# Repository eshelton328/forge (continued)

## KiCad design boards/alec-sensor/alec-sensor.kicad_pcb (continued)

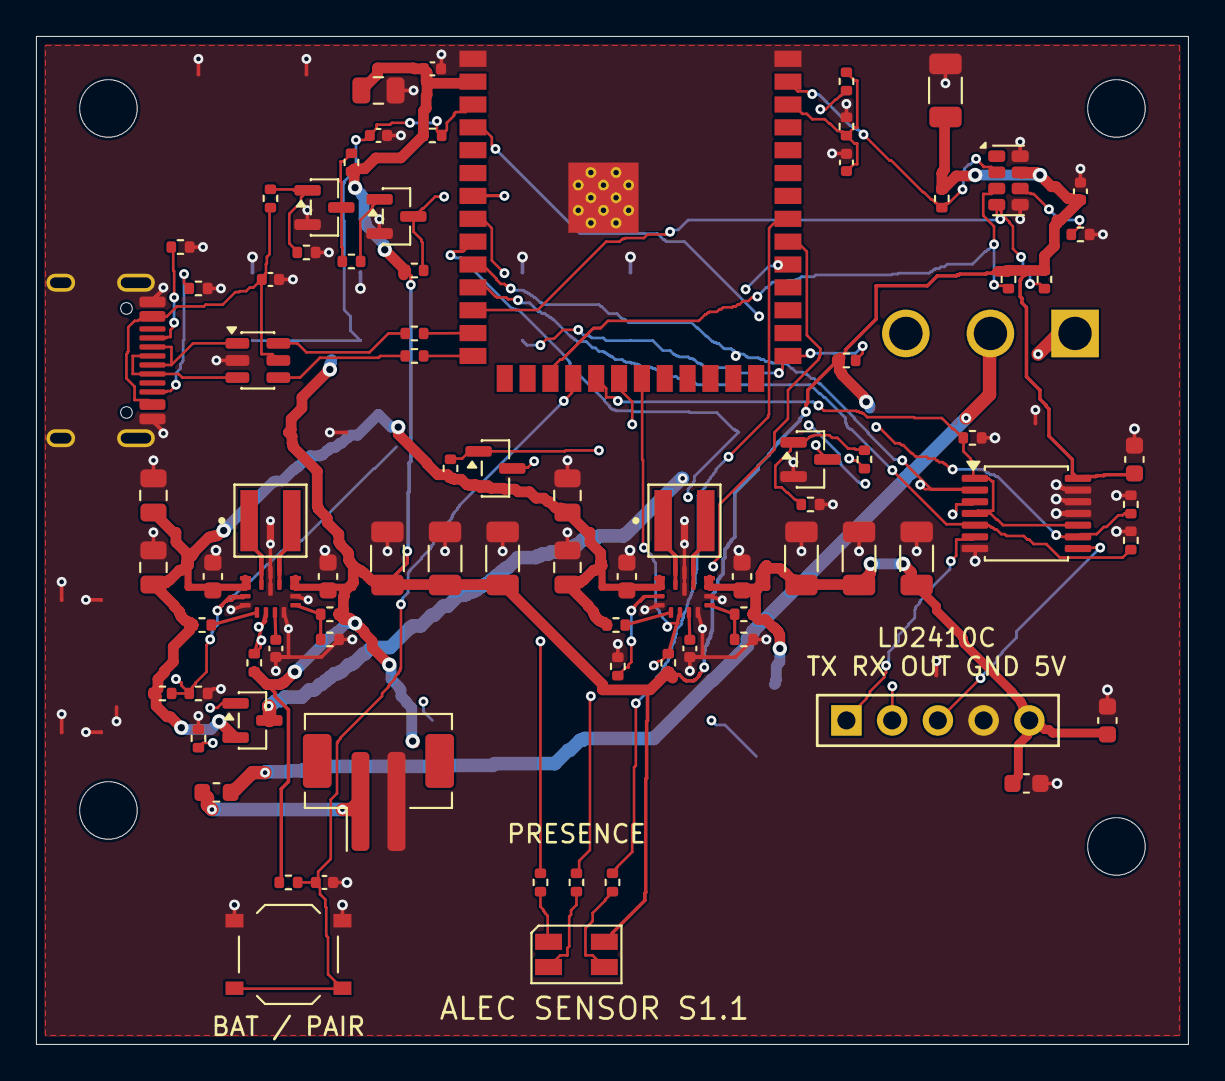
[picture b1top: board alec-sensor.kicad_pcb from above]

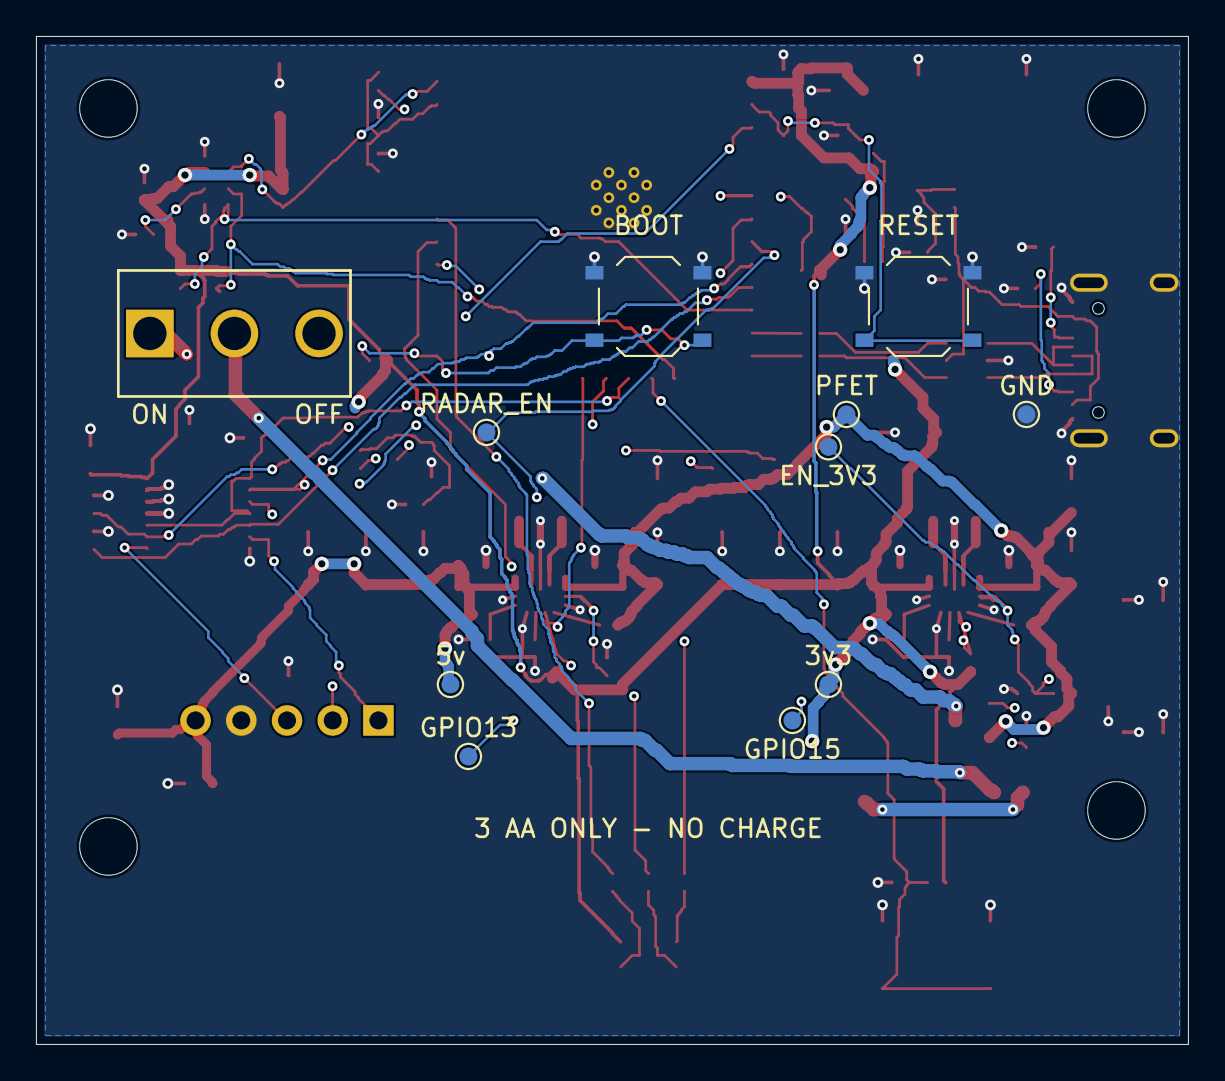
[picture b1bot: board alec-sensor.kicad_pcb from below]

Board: 4 copper layers, 64.0 x 56.0 mm, 100 parts (11 on the bottom side), 60 nets.

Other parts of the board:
H1, H2, H3, H4: M3; MountingHole_3.2mm_M3
TP1: GND; TestPoint_Pad_D1.0mm
TP2: PFET; TestPoint_Pad_D1.0mm
TP3: 3v3; TestPoint_Pad_D1.0mm
TP4: 5v; TestPoint_Pad_D1.0mm
TP5: GPIO15; TestPoint_Pad_D1.0mm
TP6: GPIO13; TestPoint_Pad_D1.0mm
TP7: EN_3V3; TestPoint_Pad_D1.0mm
TP8: RADAR_EN; TestPoint_Pad_D1.0mm

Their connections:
/3v3: TP3.1; also elsewhere on the board
/5v: TP4.1; also elsewhere on the board
/EN_3V3: TP7.1; also elsewhere on the board
/GPIO13: TP6.1; also elsewhere on the board
/GPIO15: TP5.1; also elsewhere on the board
/PFET: TP2.1; also elsewhere on the board
/RADAR_EN: TP8.1; also elsewhere on the board
GND: TP1.1; also elsewhere on the board

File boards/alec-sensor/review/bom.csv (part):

Reference,Value,MPN,Footprint,Voltage,Datasheet,Assembly,Manufacturer,LCSC#
C1,10µF,GRM21BR61E106KA73L,Capacitor_SMD:C_0805_2012Metric,25V,https://www.lcsc.com/datasheet/lcsc_datasheet_2304140030_Mur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,Selected prototype part; package/assembly release checks remain,Murata Electronics,C84416
C10,10µF,GRM21BR61E106KA73L,Capacitor_SMD:C_0805_2012Metric,25V,https://www.lcsc.com/datasheet/lcsc_datasheet_2304140030_Mur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,Selected prototype part; package/assembly release checks remain,Murata Electronics,C84416
C11,10µF,GRT188R61A106KE13D,Capacitor_SMD:C_0603_1608Metric,10V,https://search.murata.co.jp/Ceramy/image/img/A01X/G101/ENG/G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,Selected prototype part; package/assembly release checks remain,Murata Electronics,C782172
C12,0.1µF,GRM155R71C104KA88D,Capacitor_SMD:C_0402_1005Metric,16V,https://www.lcsc.com/datasheet/lcsc_datasheet_1811081616_Mur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,Selected prototype part; package/assembly release checks remain,Murata Electronics,C71629
C13,10µF,GRT188R61A106KE13D,Capacitor_SMD:C_0603_1608Metric,10V,https://search.murata.co.jp/Ceramy/image/img/A01X/G101/ENG/G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,Selected prototype part; package/assembly release checks remain,Murata Electronics,C782172
C14,22µF,GRM31CR61C226KE15L,Capacitor_SMD:C_1206_3216Metric,16V,https://www.lcsc.com/datasheet/lcsc_datasheet_2304140030_Mur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,Selected prototype part; package/assembly release checks remain,Murata Electronics,C77088
C15,22µF,GRM31CR61C226KE15L,Capacitor_SMD:C_1206_3216Metric,16V,https://www.lcsc.com/datasheet/lcsc_datasheet_2304140030_Mur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,Selected prototype part; package/assembly release checks remain,Murata Electronics,C77088
C16,22µF,GRM31CR61C226KE15L,Capacitor_SMD:C_1206_3216Metric,16V,https://www.lcsc.com/datasheet/lcsc_datasheet_2304140030_Mur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,Selected prototype part; package/assembly release checks remain,Murata Electronics,C77088
C17,22µF,GRM21BR61A226ME44L,Capacitor_SMD:C_0805_2012Metric,10V,https://www.lcsc.com/datasheet/lcsc_datasheet_2410010301_Mur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,Selected prototype part; package/assembly release checks remain,Murata Electronics,C441864
C18,0.1µF,GRM155R71C104KA88D,Capacitor_SMD:C_0402_1005Metric,16V,https://www.lcsc.com/datasheet/lcsc_datasheet_1811081616_Mur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,Selected prototype part; package/assembly release checks remain,Murata Electronics,C71629
C19,1µF,GRM155R61A105KE15D,Capacitor_SMD:C_0402_1005Metric,10V,https://www.lcsc.com/datasheet/lcsc_datasheet_1810201320_Mur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,Selected prototype part; package/assembly release checks remain,Murata Electronics,C76999
C2,10µF,GRM21BR61E106KA73L,Capacitor_SMD:C_0805_2012Metric,25V,https://www.lcsc.com/datasheet/lcsc_datasheet_2304140030_Mur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,Selected prototype part; package/assembly release checks remain,Murata Electronics,C84416
C20,0.1µF,GRM155R71C104KA88D,Capacitor_SMD:C_0402_1005Metric,16V,https://www.lcsc.com/datasheet/lcsc_datasheet_1811081616_Mur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,Selected prototype part; package/assembly release checks remain,Murata Electronics,C71629
C21,100µF,CL31A107MQHNNNE,Capacitor_SMD:C_1206_3216Metric,6.3V,https://www.lcsc.com/datasheet/lcsc_datasheet_2304140030_Sam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,Selected prototype part; package/assembly release checks remain,Samsung Electro-Mechanics,C15008
C25,0.1µF,GRM155R71C104KA88D,Capacitor_SMD:C_0402_1005Metric,16V,https://www.lcsc.com/datasheet/lcsc_datasheet_1811081616_Mur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,Selected prototype part; package/assembly release checks remain,Murata Electronics,C71629
C29,0.1µF,GRM155R71C104KA88D,Capacitor_SMD:C_0402_1005Metric,16V,https://www.lcsc.com/datasheet/lcsc_datasheet_1811081616_Mur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,Selected prototype part; package/assembly release checks remain,Murata Electronics,C71629
C3,10µF,GRT188R61A106KE13D,Capacitor_SMD:C_0603_1608Metric,10V,https://search.murata.co.jp/Ceramy/image/img/A01X/G101/ENG/G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,Selected prototype part; package/assembly release checks remain,Murata Electronics,C782172
C34,0.1uF,GRM155R71C104KA88D,Capacitor_SMD:C_0402_1005Metric,16V,https://www.lcsc.com/datasheet/lcsc_datasheet_1811081616_Mur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,Selected prototype part; package/assembly release checks remain,Murata Electronics,C71629
C35,10uF,GRT188R61A106KE13D,Capacitor_SMD:C_0603_1608Metric,10V,https://search.murata.co.jp/Ceramy/image/img/A01X/G101/ENG/G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,Selected prototype part; package/assembly release checks remain,Murata Electronics,C782172
C36,0.1uF,GRM188R71C104KA01D,Capacitor_SMD:C_0603_1608Metric,16V,https://wmsc.lcsc.com/wmsc/upload/file/pdf/v2/lcsc/181031111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,Selected prototype part; package/assembly release checks remain,Murata Electronics,C45000
C37,0.1uF,GRM188R71C104KA01D,Capacitor_SMD:C_0603_1608Metric,16V,https://wmsc.lcsc.com/wmsc/upload/file/pdf/v2/lcsc/181031111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,Selected prototype part; package/assembly release checks remain,Murata Electronics,C45000
C4,0.1µF,GRM155R71C104KA88D,Capacitor_SMD:C_0402_1005Metric,16V,https://www.lcsc.com/datasheet/lcsc_datasheet_1811081616_Mur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,Selected prototype part; package/assembly release checks remain,Murata Electronics,C71629
C5,10µF,GRT188R61A106KE13D,Capacitor_SMD:C_0603_1608Metric,10V,https://search.murata.co.jp/Ceramy/image/img/A01X/G101/ENG/G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,Selected prototype part; package/assembly release checks remain,Murata Electronics,C782172
C6,22µF,GRM31CR61C226KE15L,Capacitor_SMD:C_1206_3216Metric,16V,https://www.lcsc.com/datasheet/lcsc_datasheet_2304140030_Mur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,Selected prototype part; package/assembly release checks remain,Murata Electronics,C77088
C7,22µF,GRM31CR61C226KE15L,Capacitor_SMD:C_1206_3216Metric,16V,https://www.lcsc.com/datasheet/lcsc_datasheet_2304140030_Mur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,Selected prototype part; package/assembly release checks remain,Murata Electronics,C77088
C8,22µF,GRM31CR61C226KE15L,Capacitor_SMD:C_1206_3216Metric,16V,https://www.lcsc.com/datasheet/lcsc_datasheet_2304140030_Mur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,Selected prototype part; package/assembly release checks remain,Murata Electronics,C77088
C9,10µF,GRM21BR61E106KA73L,Capacitor_SMD:C_0805_2012Metric,25V,https://www.lcsc.com/datasheet/lcsc_datasheet_2304140030_Mur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,Selected prototype part; package/assembly release checks remain,Murata Electronics,C84416
D2,150141M173100,150141M173100,LED_SMD:LED_RGB_Wuerth-PLCC4_3.2x2.8mm_150141M173100,,https://www.we-online.com/components/products/datasheet/1501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,Selected prototype part; package/assembly release checks remain,Wurth Elektronik,C5342281
F1,1.5A FAST,046701.5NRHF,Fuse:Fuse_0603_1608Metric,,https://www.lcsc.com/datasheet/lcsc_datasheet_2304140030_Lit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,Selected prototype part; package/assembly release checks remain,Littelfuse,C187608
J1,Conn_01x02_Pin,B2B-PH-SM4-TB(LF)(SN),Connector_JST:JST_PH_B2B-PH-SM4-TB_1x02-1MP_P2.00mm_Vertical,,https://www.lcsc.com/datasheet/lcsc_datasheet_2304140030_JST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,Selected prototype part; package/assembly release checks remain,JST,C160352
J2,USB_C_Receptacle_USB2.0_16P,TYPE-C-31-M-12,Board:USB_C_HRO_Overhang,,https://www.lcsc.com/datasheet/lcsc_datasheet_2205251630_Kor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,Selected prototype part; package/assembly release checks remain,Korean Hroparts Elec,C165948
J3,LD2410C — INTERNAL,SSW-105-01-F-S,Sensor:Samtec_SSW-105-01-F-S,,https://www.samtec.com/products/ssw-105-01-f-s,Selected prototype part; package/assembly release checks remain,Samtec,C5930350
L1,1.5µH,XFL4020-152MEC,TPS63070:IND_XFL4020-152MEC,,https://www.coilcraft.com/getmedia/50632d43-da1b-4cdb-8ab4-3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,Selected prototype part; package/assembly release checks remain,Coilcraft,C3033018
L2,1.5µH,XFL4020-152MEC,TPS63070:IND_XFL4020-152MEC,,https://www.coilcraft.com/getmedia/50632d43-da1b-4cdb-8ab4-3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,Selected prototype part; package/assembly release checks remain,Coilcraft,C3033018
Q1,AO3401A,AO3401A,Package_TO_SOT_SMD:SOT-23,,https://www.lcsc.com/datasheet/lcsc_datasheet_2412061733_Alp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,Selected prototype part; package/assembly release checks remain,Alpha & Omega Semicon,C15127
Q4,MMBT3904,MMBT3904LT1G,Package_TO_SOT_SMD:SOT-23,,https://www.onsemi.com/pdf/datasheet/mmbt3904lt1-d.pdf,Selected prototype part; package/assembly release checks remain,onsemi,C81464
Q5,MMBT3904,MMBT3904LT1G,Package_TO_SOT_SMD:SOT-23,,https://www.onsemi.com/pdf/datasheet/mmbt3904lt1-d.pdf,Selected prototype part; package/assembly release checks remain,onsemi,C81464
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
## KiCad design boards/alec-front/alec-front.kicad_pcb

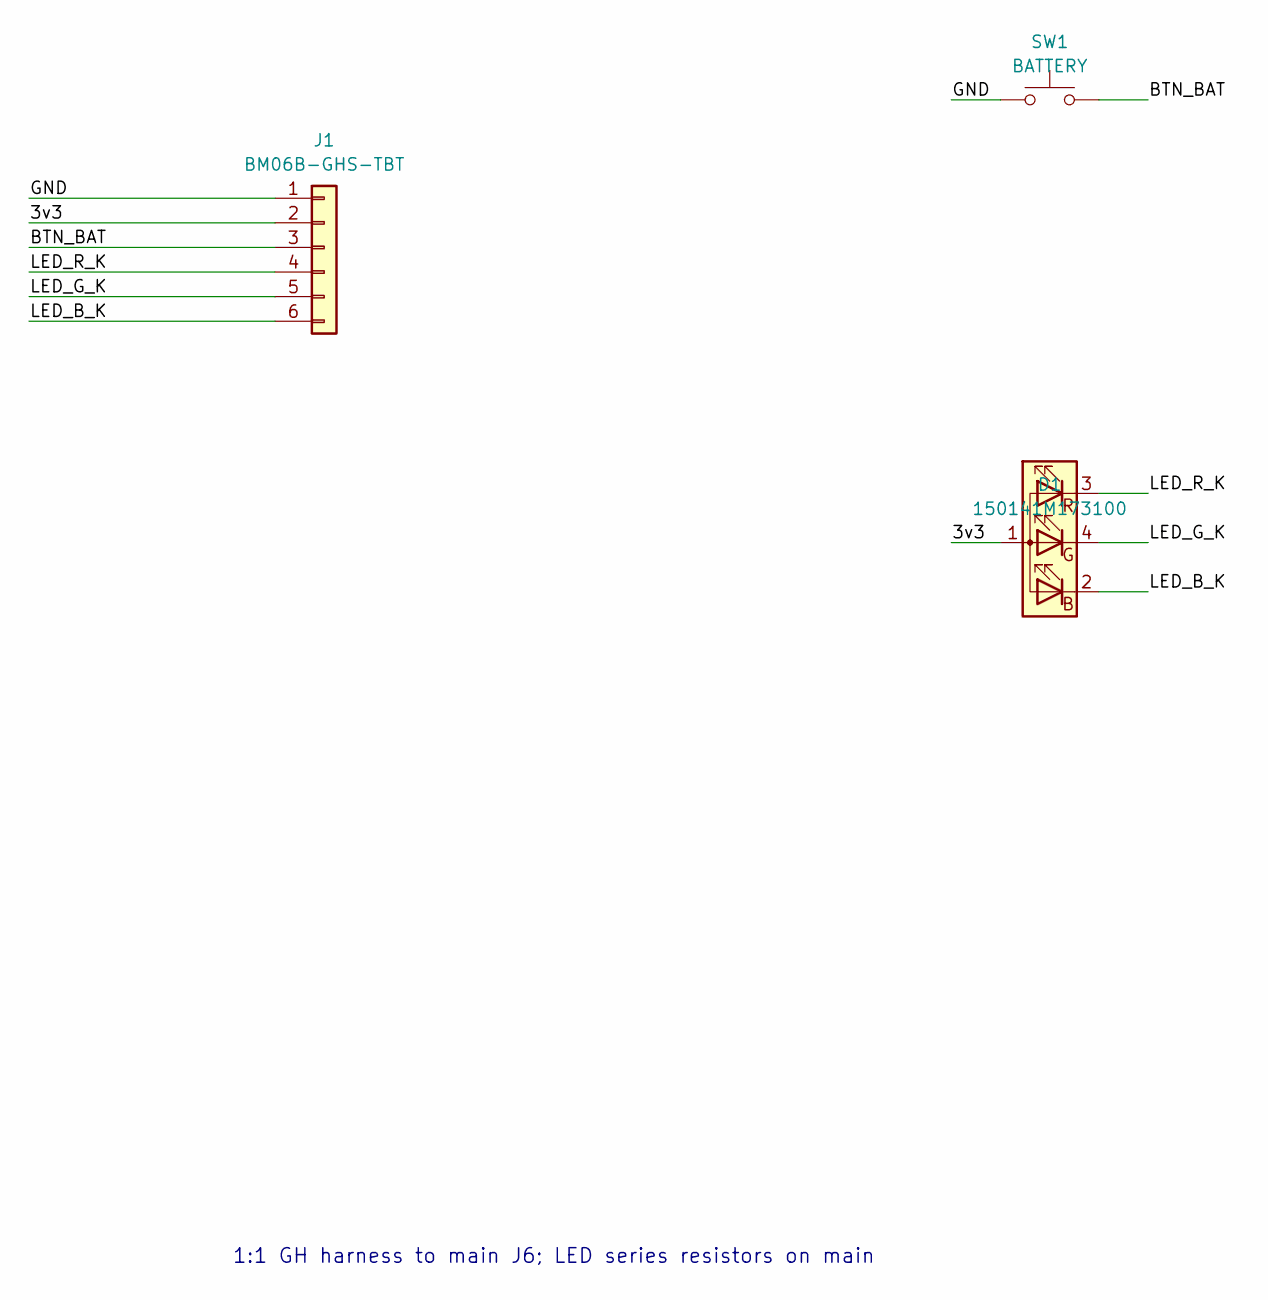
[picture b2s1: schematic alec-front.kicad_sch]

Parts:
D1: 150141M173100; LED_RGB_Wuerth-PLCC4_3.2x2.8mm_150141M173100; MPN 150141M173100; LCSC# C5342281
J1: BM06B-GHS-TBT; JST_GH_BM06B-GHS-TBT_1x06-1MP_P1.25mm_Vertical; MPN BM06B-GHS-TBT(LF)(SN); LCSC# C189892
SW1: BATTERY; SW_SPST_B3U-1000P; MPN B3U-1000P; LCSC# C231329

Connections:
/3v3: D1.1 (A), J1.2
/BTN_BAT: J1.3, SW1.2
/GND: J1.1, SW1.1
/LED_B_K: D1.2 (BK), J1.6
/LED_G_K: D1.4 (GK), J1.5
/LED_R_K: D1.3 (RK), J1.4

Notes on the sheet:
1:1 GH harness to main J6; LED series resistors on main

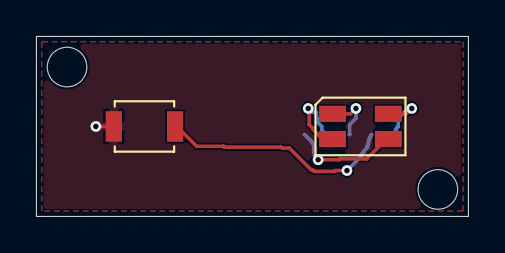
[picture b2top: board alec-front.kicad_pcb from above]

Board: 2 copper layers, 24.0 x 10.0 mm, 5 parts (1 on the bottom side), 6 nets.

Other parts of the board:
H1, H2: MountingHole_2.2mm_M2

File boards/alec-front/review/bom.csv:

Reference,Value,MPN,Footprint,Voltage,Datasheet,Assembly,Manufacturer,LCSC#
D1,150141M173100,150141M173100,LED_SMD:LED_RGB_Wuerth-PLCC4_3.2x2.8mm_150141M173100,,https://www.we-online.com/components/products/datasheet/1501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,Selected prototype part; package/assembly release checks remain,Wurth Elektronik,C5342281
J1,BM06B-GHS-TBT,BM06B-GHS-TBT(LF)(SN),Connector_JST:JST_GH_BM06B-GHS-TBT_1x06-1MP_P1.25mm_Vertical,,https://www.jst-mfg.com/product/pdf/eng/eGH.pdf,Selected prototype part; package/assembly release checks remain,JST,C189892
SW1,BATTERY,B3U-1000P,Button_Switch_SMD:SW_SPST_B3U-1000P,,https://omronfs.omron.com/en_US/ecb/products/pdf/en-b3u.pdf,Selected prototype part; package/assembly release checks remain,Omron Electronics,C231329

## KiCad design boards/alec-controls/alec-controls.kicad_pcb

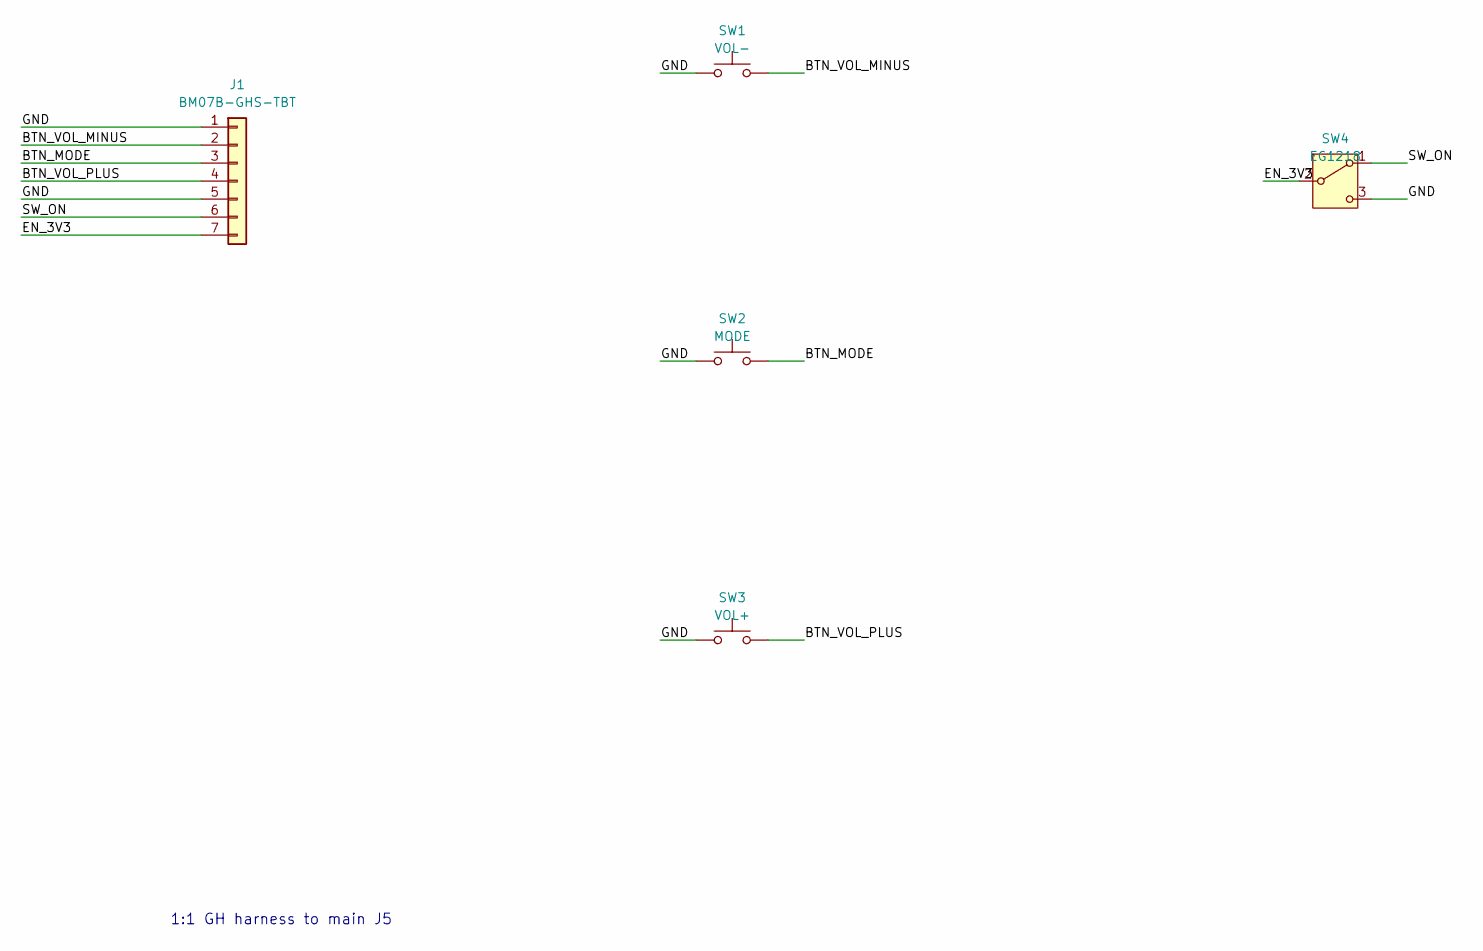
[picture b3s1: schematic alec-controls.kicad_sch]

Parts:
J1: BM07B-GHS-TBT; JST_GH_BM07B-GHS-TBT_1x07-1MP_P1.25mm_Vertical; MPN BM07B-GHS-TBT(LF)(SN); LCSC# C5305068
SW1: VOL-; SW_TH_Tactile_Omron_B3F-106x; MPN B3F-1060; LCSC# C726010
SW2: MODE; SW_TH_Tactile_Omron_B3F-106x; MPN B3F-1060; LCSC# C726010
SW3: VOL+; SW_TH_Tactile_Omron_B3F-106x; MPN B3F-1060; LCSC# C726010
SW4: EG1218; MPN EG1218; LCSC# C273394

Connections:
/BTN_MODE: J1.3, SW2.2
/BTN_VOL_MINUS: J1.2, SW1.2
/BTN_VOL_PLUS: J1.4, SW3.2
/EN_3V3: J1.7, SW4.2 (B)
/GND: J1.1, J1.5, SW1.1, SW2.1, SW3.1, SW4.3 (C)
/SW_ON: J1.6, SW4.1 (A)

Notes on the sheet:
1:1 GH harness to main J5

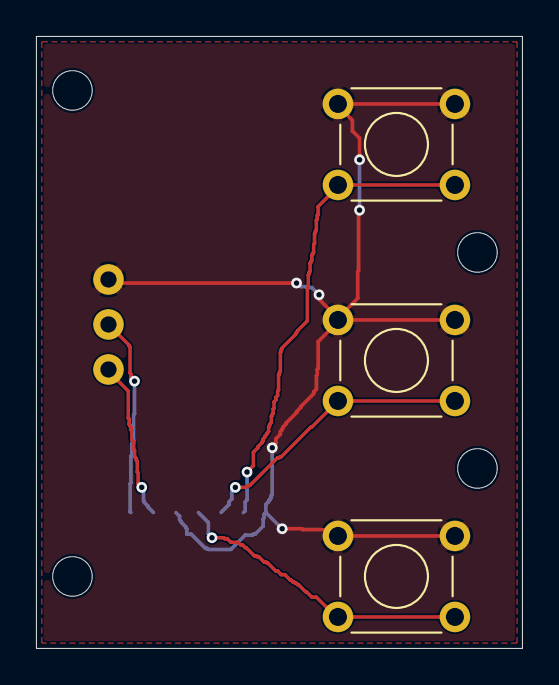
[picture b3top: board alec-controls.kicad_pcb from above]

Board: 2 copper layers, 27.0 x 34.0 mm, 9 parts (1 on the bottom side), 6 nets.

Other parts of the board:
H1, H2, H3, H4: MountingHole_2.2mm_M2

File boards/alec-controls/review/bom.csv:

Reference,Value,MPN,Footprint,Voltage,Datasheet,Assembly,Manufacturer,LCSC#
J1,BM07B-GHS-TBT,BM07B-GHS-TBT(LF)(SN),Connector_JST:JST_GH_BM07B-GHS-TBT_1x07-1MP_P1.25mm_Vertical,,https://www.jst-mfg.com/product/pdf/eng/eGH.pdf,Selected prototype part; package/assembly release checks remain,JST,C5305068
SW1,VOL-,B3F-1060,Button_Switch_THT:SW_TH_Tactile_Omron_B3F-106x,,https://www.lcsc.com/datasheet/lcsc_datasheet_2304140030_Omr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,Selected prototype part; package/assembly release checks remain,Omron Electronics,C726010
SW2,MODE,B3F-1060,Button_Switch_THT:SW_TH_Tactile_Omron_B3F-106x,,https://www.lcsc.com/datasheet/lcsc_datasheet_2304140030_Omr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,Selected prototype part; package/assembly release checks remain,Omron Electronics,C726010
SW3,VOL+,B3F-1060,Button_Switch_THT:SW_TH_Tactile_Omron_B3F-106x,,https://www.lcsc.com/datasheet/lcsc_datasheet_2304140030_Omr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,Selected prototype part; package/assembly release checks remain,Omron Electronics,C726010
SW4,EG1218,EG1218,Alarm:EG1218,,https://www.lcsc.com/datasheet/lcsc_datasheet_1810091750_E-S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,Selected prototype part; package/assembly release checks remain,E-Switch,C273394

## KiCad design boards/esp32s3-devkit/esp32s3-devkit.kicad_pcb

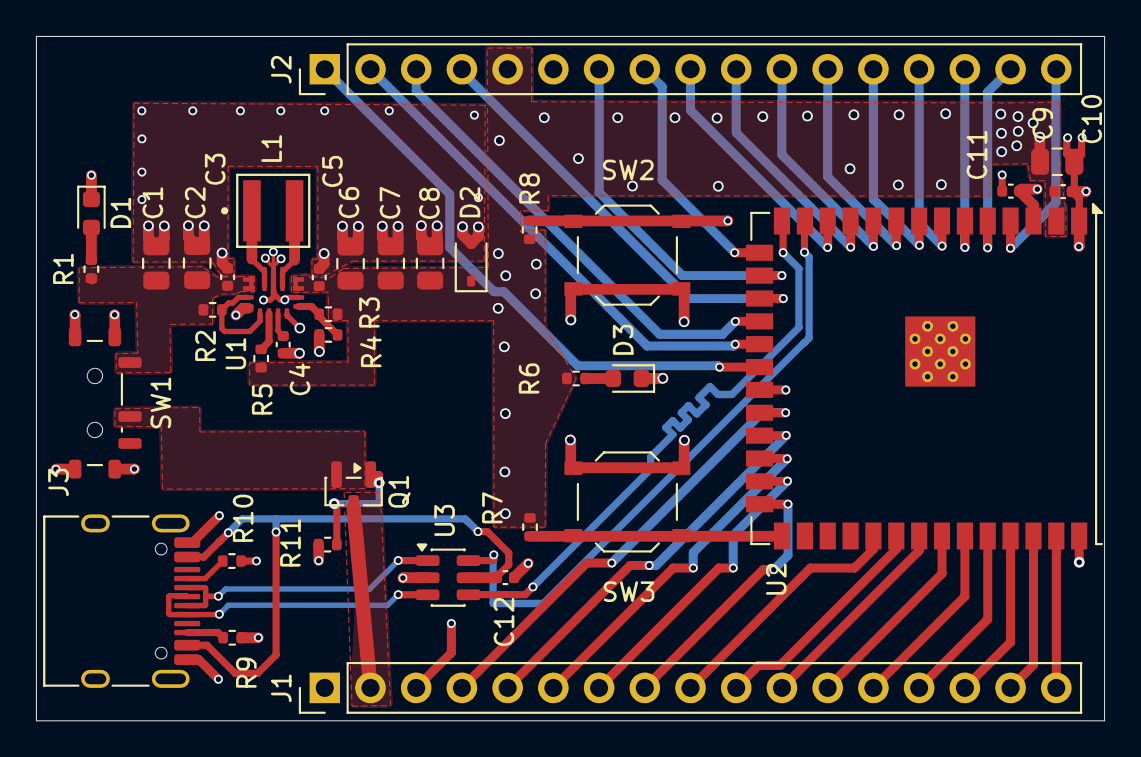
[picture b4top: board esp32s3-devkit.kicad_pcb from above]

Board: 4 copper layers, 59.3 x 38.0 mm, 37 parts (0 on the bottom side), 53 nets.

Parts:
C1, C2: 10µF; C_0805_2012Metric
C3, C5: 10µF; C_0402_1005Metric
C4, C10, C12: 0.1µF; C_0402_1005Metric
C6, C7, C8, C9: 22µF; C_0805_2012Metric
C11: 1µF; C_0402_1005Metric
D1, D3: LED; LED_0603_1608Metric
D2: 3.6v; D_SOD-323
J1, J2: Conn_01x17_Pin; PinHeader_1x17_P2.54mm_Vertical
J3: USB_C_Receptacle_USB2.0_16P; USB_C_Receptacle_HRO_TYPE-C-31-M-12
L1: 1.5µH; IND_XFL4020-152MEC
Q1: AO3401A; SOT-23
R1, R6: 1kΩ; R_0402_1005Metric
R2, R7, R8: 10kΩ; R_0402_1005Metric
R3: 470kΩ; R_0402_1005Metric
R4: 150kΩ; R_0402_1005Metric
R5, R11: 100kΩ; R_0402_1005Metric
R9, R10: 5.1kΩ; R_0402_1005Metric
SW1: MK-12C03-G015; SW_SPDT_Shouhan_MSK12C02
SW2: RESET; SW_Push_1P1T_XKB_TS-1187A
SW3: BOOT; SW_Push_1P1T_XKB_TS-1187A
U1: TPS63070RNMR; TPS63070
U2: ESP32-S3-WROOM-1-N16; ESP32-S3-WROOM-1
U3: USBLC6-2SC6; SOT-23-6

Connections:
/3v3: C5.1, C6.1, C7.1, C8.1, C9.1, C10.1, D2.1 (K), J2.5, R3.1, R5.1, R6.1, R7.1, R8.1, U1.7 (VOUT), U1.8 (VOUT), U2.2 (3V3)
/D+: U2.14 (USB_D+), U3.4 (I/O2)
/D-: U2.13 (USB_D-), U3.6 (I/O1)
/GPIO1: J1.17, U2.39 (IO1)
/GPIO2: J1.16, U2.38 (IO2)
/GPIO3: J2.8, U2.15 (IO3)
/GPIO4: J2.17, U2.4 (IO4)
/GPIO5: J2.16, U2.5 (IO5)
/GPIO6: J2.15, U2.6 (IO6)
/GPIO7: J2.14, U2.7 (IO7)
/GPIO8: J2.9, U2.12 (IO8)
/GPIO9: J2.4, U2.17 (IO9)
/GPIO10: J2.3, U2.18 (IO10)
/GPIO11: J2.2, U2.19 (IO11)
/GPIO12: J2.1, U2.20 (IO12)
/GPIO13: J1.3, U2.21 (IO13)
/GPIO14: J1.4, U2.22 (IO14)
/GPIO15: J2.13, U2.8 (IO15)
/GPIO16: J2.12, U2.9 (IO16)
/GPIO17: J2.11, U2.10 (IO17)
/GPIO18: J2.10, U2.11 (IO18)
/GPIO21: J1.5, U2.23 (IO21)
/GPIO38: J1.9, U2.31 (IO38)
/GPIO39: J1.10, U2.32 (IO39)
/GPIO40: J1.11, U2.33 (IO40)
/GPIO41: J1.12, U2.34 (IO41)
/GPIO42: J1.13, U2.35 (IO42)
/GPIO45: J1.8, U2.26 (IO45)
/GPIO46: J2.7, U2.16 (IO46)
/GPIO47: J1.6, U2.24 (IO47)
/GPIO48: J1.7, U2.25 (IO48)
/PFET: Q1.2 (S), SW1.2 (B)
/RX: J1.14, U2.36 (RXD0)
/TX: J1.15, U2.37 (TXD0)
/VBAT: J1.2, Q1.3 (D)
/VBAT_SW: C1.1, C2.1, C3.1, R1.1, R2.1, SW1.1 (A), U1.12 (VIN), U1.13 (VIN)
GND: C1.2, C2.2, C3.2, C4.2, C5.2, C6.2, C7.2, C8.2, C9.2, C10.2, C11.2, C12.2, D1.1 (K), D2.2 (A), D3.1 (K), J1.1, J2.6, J3.A1 (GND), J3.A12 (GND), J3.B1 (GND), J3.B12 (GND), J3.SH (SHIELD), R4.2, R9.2, R10.2, R11.2, SW1.SH (SHIELD), SW2.1, SW3.1, U1.4 (GND), U1.6 (FB2), U1.10 (PGND), U1.15 (VSEL), U2.1 (GND), U2.40 (GND), U2.41 (GND), U3.2 (GND)
unnamed: D1.2 (A), R1.2
unnamed: D3.2 (A), R6.2
unnamed: J3.A5 (CC1), R10.1
unnamed: J3.B5 (CC2), R9.1
unnamed: J3.A6 (D+), J3.B6 (D+), U3.3 (I/O2)
unnamed: J3.A7 (D-), J3.B7 (D-), U3.1 (I/O1)
unnamed: Q1.1 (G), R11.1
unnamed: R2.2, U1.1 (PS_SYNC), U1.14 (EN)
unnamed: R3.2, R4.1, U1.5 (FB)
unnamed: L1.1, U1.11 (L1)
unnamed: L1.2, U1.9 (L2)
unnamed: R5.2, U1.2 (PG)
unnamed: C4.1, U1.3 (VAUX)
unnamed: C11.1, R8.2, SW2.2, U2.3 (EN)
unnamed: R7.2, SW3.2, U2.27 (IO0)
unnamed: C12.1, J3.A4 (VBUS), J3.A9 (VBUS), J3.B4 (VBUS), J3.B9 (VBUS), U3.5 (VBUS)

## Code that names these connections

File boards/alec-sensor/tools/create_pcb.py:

#!/usr/bin/env python3
"""Build S1 from reviewed copper. Run with KiCad Python; route low-speed additions next.
No switching-cell footprint or local copper is moved. See migration.json for net edits.
"""
from pathlib import Path
import sys, shutil, json, xml.etree.ElementTree as E
import wx
app=wx.App(False)
import pcbnew as p
ROOT=Path(__file__).resolve().parents[3];D=Path(__file__).resolve().parents[1]
sys.path.insert(0,str(ROOT/'scripts/alarm'))
from design import BASE,LIB
V=lambda x,y:p.VECTOR2I(p.FromMM(x),p.FromMM(y))
def layers(*ll):
 s=p.LSET()
 for l in ll:s.AddLayer(l)
 return s
FP=D/'footprints/Sensor.pretty';FP.mkdir(parents=True,exist_ok=True)
shutil.copytree(BASE/'footprints/Board.pretty',D/'footprints/Board.pretty',dirs_exist_ok=True)
(D/'3dmodels').mkdir(exist_ok=True)
for model in (BASE/'3dmodels').iterdir():
 if model.suffix.lower() in ['.step','.wrl'] or model.name.startswith('LICENSE-'):shutil.copy2(model,D/'3dmodels'/model.name)
def rect(f,l,x1,y1,x2,y2):
 for a,c in [((x1,y1),(x2,y1)),((x2,y1),(x2,y2)),((x2,y2),(x1,y2)),((x1,y2),(x1,y1))]:
  g=p.PCB_SHAPE(f);g.SetShape(p.SHAPE_T_SEGMENT);g.SetStart(V(*a));g.SetEnd(V(*c));g.SetLayer(l);g.SetWidth(p.FromMM(.05 if l==p.F_CrtYd else .15));f.Add(g)
for name in ['SW_CK_1101M2S3CQE2','Samtec_SSW-105-01-F-S']:
 f=p.FOOTPRINT(None);f.SetFPID(p.LIB_ID('Sensor',name));f.SetReference('REF**');f.SetValue(name);f.SetAttributes(p.FP_THROUGH_HOLE)
 if name.startswith('SW_'):
  pos=[(-4.7,0),(0,0),(4.7,0)];size=2.65;drill=1.85;bounds=(-6.35,-3.3,6.35,3.3)
 else:
  pos=[(i*2.54,0) for i in range(5)];size=1.7;drill=1.0;bounds=(-1.525,-1.205,11.685,1.205)
 for i,(x,y) in enumerate(pos,1):
  pad=p.PAD(f);pad.SetNumber(str(i));pad.SetPosition(V(x,y));pad.SetShape(p.PAD_SHAPE_RECT if i==1 else p.PAD_SHAPE_CIRCLE);pad.SetAttribute(p.PAD_ATTRIB_PTH);pad.SetSize(V(size,size));pad.SetDrillSize(V(drill,drill));pad.SetLayerSet(p.PAD.PTHMask());f.Add(pad)
 rect(f,p.F_Fab,*bounds);rect(f,p.F_CrtYd,bounds[0]-.5,bounds[1]-.5,bounds[2]+.5,bounds[3]+.5)
 rect(f,p.F_SilkS,bounds[0]-.1,bounds[1]-.2,bounds[2]+.1,bounds[3]+.2)
 model=p.FP_3DMODEL();model.m_Filename='${KIPRJMOD}/3dmodels/'+name+'.step';f.Add3DModel(model)
 p.PCB_IO_KICAD_SEXPR().FootprintSave(str(FP),f)
xml=E.parse(D/'review/netlist.xml').getroot();comps={c.get('ref'):c for c in xml.find('components')};pn={}
for n in xml.find('nets'):
 for a in n:pn[a.get('ref'),a.get('pin')]=n.get('name')
b=p.LoadBoard(str(BASE/(BASE.name+'.kicad_pcb')));oldfps={f.GetReference():f for f in b.GetFootprints()}
oldpn={(ref,a.GetNumber()):a.GetNetname() for ref,f in oldfps.items() for a in f.Pads()}
replace={'SW1','J3','SW7'} # SW7 schematic B3U footprint differs from base PCB TS1187
moved={'D2','R28','R29','R30','SW2','SW3','R27','C25'}
removed=[];discarded=[]
for ref,f in oldfps.items():
 if ref in replace or (ref not in comps and not ref.startswith(('H','TP'))):b.Remove(f);discarded.append(f);removed.append(ref)
# Schematic same-net mapping must be unambiguous before any retained track is relabelled.
mapsets={}
for key,new in pn.items():
 if key in oldpn and key[0] not in replace:mapsets.setdefault(oldpn[key],set()).add(new)
renames={old:next(iter(nn)) for old,nn in mapsets.items() if len(nn)==1}
reroute={'/VBAT','/GPIO18','/SW_ON','/GPIO4','/GPIO10','/GPIO11','/GPIO17','/LED_R_K','/LED_G_K','/LED_B_K','/GPIO38','/GPIO39','/GPIO40','/GPIO0','/GPIO8','/GPIO9'}
reroute.update(old for (ref,pin),old in oldpn.items() if ref in moved|replace and old not in ['GND','/3v3','/5v','/PFET'])
# Keep power nets and critical USB/local regulator traces, remove conductors for retired signals.
override_tracks={}
netnames={n.get('name') for n in xml.find('nets')};removed_tracks=0
for t in list(b.GetTracks()):
 old=t.GetNetname();new=renames.get(old,old)
 if old in ['/EN_3V3','/SW_ON']:
  override_tracks[t.m_Uuid.AsString()]='/EN_3V3';continue
 if old=='/GPIO18' and min(p.ToMM(t.GetStart().y),p.ToMM(t.GetEnd().y))>=90:
  override_tracks[t.m_Uuid.AsString()]='/RADAR_EN';continue
 if old=='/GPIO38' and max(p.ToMM(t.GetStart().y),p.ToMM(t.GetEnd().y))<85:continue
 retired_area=(min(p.ToMM(t.GetStart().x),p.ToMM(t.GetEnd().x))>150 and min(p.ToMM(t.GetStart().y),p.ToMM(t.GetEnd().y))>92) or (min(p.ToMM(t.GetStart().x),p.ToMM(t.GetEnd().x))>142 and min(p.ToMM(t.GetStart().y),p.ToMM(t.GetEnd().y))>106)
 if old in reroute or new not in netnames or new.startswith('unconnected-') or len(mapsets.get(old,set()))>1 or retired_area:
  b.Remove(t);discarded.append(t);removed_tracks+=1
# Discard local supply stubs at moved/removed components in the southern former UI region.
for t in list(b.GetTracks()):
 if min(p.ToMM(t.GetStart().y),p.ToMM(t.GetEnd().y))>=111 and t.GetNetname() in ['GND','/3v3']:
  b.Remove(t);discarded.append(t);removed_tracks+=1
nets={}
for name in netnames:
 ni=next((v for v in b.GetNetsByNetcode().values() if v.GetNetname()==name),None)
 if ni is None:ni=p.NETINFO_ITEM(b,name);b.Add(ni)
 nets[name]=ni
for t in b.GetTracks():
 name=override_tracks.get(t.m_Uuid.AsString(),renames.get(t.GetNetname(),t.GetNetname()))
 if name in nets:t.SetNet(nets[name])
for f in b.GetFootprints():
 for pad in f.Pads():
  key=f.GetReference(),pad.GetNumber()
  if key in pn:pad.SetNet(nets[pn[key]])
  elif f.GetReference()=='TP8':pad.SetNet(nets['/RADAR_EN']);f.SetValue('RADAR_EN')
 f.SetSheetfile(D.name+'.kicad_sch')
positions={'SW1':(153,89.5,0),'SW3':(152,120,0),'SW7':(114,121,0),'D2':(130,121,0),'R28':(128,117,90),'R29':(130,117,90),'R30':(132,117,90),'R27':(114,117,0),'C25':(116,117,0),'F1':(110,112,0),'U10':(155,96.5,0),'J3':(145,108,0),'C35':(155,111.5,0),'C36':(159.5,108,90),'C37':(161,93.5,90),'R54':(152,92.3,0),'R55':(160.8,96,90),'R56':(160.8,98,90)}
interface=json.loads((ROOT/'enclosures/alec-sensor/interface.json').read_text())
for ref,control in interface['service_controls'].items():positions[ref]=(*control['kicad_xy'],0)
for ref,c in comps.items():
 f=next((a for a in b.GetFootprints() if a.GetReference()==ref),None)
 if f is None:
  lib,name=c.findtext('footprint').split(':');folder=FP if lib=='Sensor' else D/'footprints/Board.pretty' if lib=='Board' else ROOT/'libs/footprints/TPS63070.pretty' if lib=='TPS63070' else LIB/'footprints'/f'{lib}.pretty'
  f=p.FootprintLoad(str(folder),name);assert f,ref;f.SetFPID(p.LIB_ID(lib,name));f.SetReference(ref);b.Add(f)
  updated=list(f.Models());f.Models().clear()
  for m in updated:
   src=Path(m.m_Filename.replace('${KICAD10_3DMODEL_DIR}',str(LIB/'3dmodels')).replace('${KICAD9_3DMODEL_DIR}',str(LIB/'3dmodels')))
   if src.is_file():shutil.copy2(src,D/'3dmodels'/src.name);m.m_Filename='${KIPRJMOD}/3dmodels/'+src.name
   f.Add3DModel(m)
 f.SetValue(c.findtext('value'))
 for a in c.findall('fields/field'):
  if a.get('name')!='Footprint':f.SetField(a.get('name'),a.text or '')
 path=p.KIID_PATH()
 for u in (c.find('sheetpath').get('tstamps')+c.findtext('tstamps')).strip('/').split('/'):path.push_back(p.KIID(u))
 f.SetPath(path)
 for pd in f.Pads():
  if (ref,pd.GetNumber()) in pn:pd.SetNet(nets[pn[ref,pd.GetNumber()]])
 if ref in positions:
  x,y,rot=positions[ref];f.SetPosition(V(x,y));f.SetOrientationDegrees(rot)
 if ref in interface['service_controls']:f.Flip(f.GetPosition(),False)
 for field in f.GetFields():field.SetVisible(False)
# Retired labels are not allowed to misidentify the sensor interface.
for g in list(b.GetDrawings()):
 if isinstance(g,p.PCB_TEXT):b.Remove(g);discarded.append(g)
def text(s,x,y,layer=p.F_SilkS,size=1):
 t=p.PCB_TEXT(b);t.SetText(s);t.SetPosition(V(x,y));t.SetTextSize(V(size,size));t.SetTextThickness(p.FromMM(.15));t.SetLayer(layer);t.SetMirrored(layer==p.B_SilkS);b.Add(t)
text('ALEC SENSOR S1',131,124,size=1.2)
text('BAT / PAIR',114,124);text('PRESENCE',130,118.8);text('BOOT',152,124)
text('TX RX OUT GND 5V',150,105);text('LD2410C',150,103.4)
text('3 AA ONLY - NO CHARGE',129,109.3)
text('ON',157.7,93.5,p.B_SilkS);text('OFF',148.3,93.5,p.B_SilkS)
b.BuildConnectivity();p.SaveBoard(str(D/(D.name+'.kicad_pcb')),b)
(D/'review/migration.json').write_text(json.dumps({'source_board':str(BASE.relative_to(ROOT)),'source_revision':'0bce752','removed_components':sorted(removed),'moved_low_speed_parts':positions,'removed_track_items':removed_tracks,'rerouted_original_nets':sorted(reroute),'net_renames':{k:v for k,v in renames.items() if k!=v},'power_cells':'U1/U2/L1/L2/C1-C16/R3-R10 preserved at original locations. Run check_layout.py after final routing.'},indent=2)+'\n')
print('Created PCB with',len(b.GetFootprints()),'footprints and',len(b.GetTracks()),'retained copper items')
from order_parts import synchronize_board
synchronize_board(D.name, schematics=False)

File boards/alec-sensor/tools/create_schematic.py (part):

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# Route each MCU function deliberately. Unused audio/display/button GPIOs become NC.
mcu=next(s for s in children(r,'symbol') if prop(s,'Reference')=='U3')
mx,my=map(float,child(mcu,'at')[1:3]);mpins=pins(original_defs[val(child(mcu,'lib_id')[1])])
unused=['5','6','22','23','24','25','34'] # GPIO5,6,14,21,47,48,41
for pn in unused:
 dx,dy=mpins[pn];point=(round(mx+dx,4),round(my-dy,4))
 ends={point}
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 name=val(a[1]);x,y=map(float,child(a,'at')[1:3])
 if name=='VBAT' and x>70:a[1]=q('VBAT_SW')
 if name=='SW_ON':a[1]=q('EN_3V3')
 if name=='GPIO18':a[1]=q('RADAR_EN' if x<200 else 'RADAR_RX')
 if name=='GPIO4':a[1]=q('PRESENCE_WAKE')
 if name=='GPIO11':a[1]=q('RADAR_IO_EN')
for pn,name in [('9','RADAR_EN'),('10','RADAR_TX')]: # physical module pads for IO16 / IO17
 dx,dy=mpins[pn];x,y=round(mx+dx,4),round(my-dy,4)
 for a in list(children(r,'no_connect')):
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 r.extend([wire(x,y,x-7.62,y,NAME+'radar/'+n),label(n,x-7.62,y)])
r.append(sheet)
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note(r,'3.31 V always on with SW1 closed. 4.985 V radar rail: GPIO16 high = ON.\nR19 holds radar OFF during reset; PS/SYNC high permits power-save operation.\nReserve >=200 mA at the radar connector; measure startup at depleted-cell voltage.',22.86,248,1.27)
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note(r,'RV-3028: I2C GPIO8 SDA / GPIO9 SCL; interrupt GPIO1 (active LOW).\nShort press GPIO10: battery; long press: physical pairing.\nRGB common anode; GPIO38/39/40 LOW lights R/G/B.\nNo always-on power LED. Use low-duty PWM for presence indication.',270,205,1.27)
note(r,'Prototype hardware. See TEST-REPORT.md for checks and remaining\nbench, radome, condensation and water-ingress release gates.',270,248,1.27)
# Remove cached definitions which no longer have instances.
used={val(child(s,'lib_id')[1]) for s in children(r,'symbol')}
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for i,n in enumerate(nets):
 x,y=40.64,round(27.94+i*5.08,4)
 r.extend([node(f'(hierarchical_label {q(n)} (shape bidirectional) (at {x} {y} 180) (effects (font (size 1.27 1.27)) (justify right)) (uuid {uid(NAME+"port"+n)}))'),wire(x,y,x+12.7,y,NAME+'portwire'+n),label(n,x+12.7,y)])
note(r,'LD2410C: regulated 5 V; logic is 3.3 V. J3 numbering follows the module drawing.\nThis is NOT the pin order of a generic JST cable. Verify assembled socket orientation.\nU10 opens all three signal paths when GPIO11 is low; no pull-ups on the unpowered radar side.',22.86,20.32)
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for a in children(r,'label'):
 if abs(float(child(a,'at')[1])-80.01)<0.001:
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
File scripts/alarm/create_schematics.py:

"""Create the product schematics from the reviewed bench-board circuit, deterministically."""
from design import *
import shutil,xml.etree.ElementTree as E,yaml
MAIN.mkdir(exist_ok=True)
for file in ['esp32s3-devkit-5v.kicad_pro','power-monitor.kicad_sch','sym-lib-table','fp-lib-table']:
 text=(BASE/file).read_text().replace('esp32s3-devkit-5v','alec-main')
 (MAIN/file.replace('esp32s3-devkit-5v','alec-main')).write_text(text)
for directory in ['footprints','3dmodels','models']:
 if (BASE/directory).exists():shutil.copytree(BASE/directory,MAIN/directory,dirs_exist_ok=True,ignore=shutil.ignore_patterns('model-map.json','README.md') if directory=='3dmodels' else None)
(MAIN/'review').mkdir(exist_ok=True)
shutil.copy(BASE/'review/Review.kicad_sym',MAIN/'review/Review.kicad_sym')
r=parse((BASE/'esp32s3-devkit-5v.kicad_sch').read_text().replace('esp32s3-devkit-5v','alec-main'))
child(r,'paper')[1]=q('A2')
for t in children(r,'text'):
 t[1]=q(val(t[1]).replace('SW1 selects EN_3V3: ON = PFET via R31; OFF = GND.\nBattery current bypasses SW1; this is standby, not battery isolation.', 'Setup-board SW4 via J5: ON = PFET via R31; OFF = GND.\nOnly enable current crosses the cable; OFF is standby, not isolation.').replace('D2: common anode at 3V3; RGB GPIO LOW = ON.', 'Front-board D1 via J6: common anode at 3V3; LOW = ON.'))
r.append(node('(title_block (title "ALEC main PCB") (date "2026-09-06") (rev "v4.2 prototype"))'))
netlist=E.parse(BASE/'review/netlist.xml').getroot()
netmap={(n.attrib['ref'],n.attrib['pin']):net.attrib['name'].lstrip('/') for net in netlist.find('nets') for n in net}
renames={'Net-(D2-RK)':'LED_R_K','Net-(D2-GK)':'LED_G_K','Net-(D2-BK)':'LED_B_K'}
defs={val(d[1]):d for d in children(child(r,'lib_symbols'),'symbol')}
for s in list(children(r,'symbol')):
 ref=prop(s,'Reference')
 if ref not in REMOVE:continue
 x,y,angle=map(float,child(s,'at')[1:]);assert angle==0
 for pn,(dx,dy) in pins(defs[val(child(s,'lib_id')[1])]).items():
  if (ref,pn) in netmap:
   net=netmap[ref,pn];r.append(label(renames.get(net,net),x+dx,y-dy))
  else:
   r[:]=[a for a in r if not(isinstance(a,list) and a[0]=='no_connect' and list(map(float,child(a,'at')[1:3]))==[round(x+dx,4),round(y-dy,4)])]
 r.remove(s)
# UART pins are direct module RXD0/TXD0, formerly explicitly NC.
s=next(s for s in children(r,'symbol') if prop(s,'Reference')=='U3')
x,y=map(float,child(s,'at')[1:3])
for pn,name in [('36','UART_RX'),('37','UART_TX')]:
 dx,dy=pins(defs[val(child(s,'lib_id')[1])])[pn];xx,yy=round(x+dx,4),round(y-dy,4)
 r[:]=[a for a in r if not(isinstance(a,list) and a[0]=='no_connect' and list(map(float,child(a,'at')[1:3]))==[xx,yy])]
 r.extend([wire(xx,yy,xx+5.08,yy,'UART/'+pn),label(name,xx+5.08,yy)])
# EN and IO0 use existing net names (verify the exported netlist).
for pn,name in [('3','EN'),('27','GPIO0')]:
 dx,dy=pins(defs[val(child(s,'lib_id')[1])])[pn]
 r.append(label(name,round(x+dx,4),round(y-dy,4)))
for ref,netnames,y,fp,mpn in [('J5',BOTTOM,60,gh(7),gh_mpn(7)),('J6',FRONT,115,gh(6),gh_mpn(6)),('J7',SERVICE,170,'Alarm:Programming_2x03_P2.0mm','UNPOPULATED_TEST_PADS')]:
 add_symbol(r,symbol_def('Connector_Generic',f'Conn_01x{len(netnames):02}'),ref,mpn,fp,460,y,{str(i):n for i,n in enumerate(netnames,1)},MAIN.name,'https://www.jst-mfg.com/product/pdf/eng/eGH.pdf' if ref!='J7' else '',mpn)
for i,(gpio,external) in enumerate([('GPIO4','BTN_VOL_MINUS'),('GPIO5','BTN_MODE'),('GPIO6','BTN_VOL_PLUS'),('GPIO10','BTN_BAT')],50):
 add_symbol(r,symbol_def('Device','R'),'R'+str(i),'100Ω','Resistor_SMD:R_0402_1005Metric',525,50+20*(i-50),{'1':external,'2':gpio},MAIN.name,'https://www.yageo.com/upload/media/product/productsearch/datasheet/rchip/pyu-rc-group_51_rohs_l.pdf','RC0402FR-07100RL')
for y,text in [(30,'ENCLOSURE INTERFACES — keyed GH cables, pin 1 to pin 1'),(85,'J5: VOL− / MODE / VOL+ and hardware enable; unplugged = standby'),(140,'J6: BAT button + common-anode RGB; R28–R30 remain on main board'),(192,'J7: service fixture only. 3v3 is TARGET REFERENCE, not a power input.'),(205,'UART: TX goes to programmer RX; RX to programmer TX. Use 3.3 V logic.'),(220,'OFF is standby: protected battery still feeds regulator VIN. No hard disconnect.')]:
 r.append(node(f'(text {q(text)} (at 435 {y} 0) (effects (font (size 1.5 1.5)) (justify left bottom)) (uuid {uid(text)}))'))
(MAIN/(MAIN.name+'.kicad_sch')).write_text(dump(r)+'\n')
check=yaml.safe_load((BASE/'checks.yml').read_text())
for ref in REMOVE:check['required_components'].pop(ref,None)
for ref in ['J5','J6','J7','R50','R51','R52','R53']:check['required_components'][ref]={}
(MAIN/'checks.yml').write_text(yaml.safe_dump(check,sort_keys=False,allow_unicode=True))
(MAIN/'board.yml').write_text('name: alec-main\ndescription: Enclosure main board with remote controls and UART service pads\nlayers: 4\ncopper_weight: 1oz\nthickness: 1.6mm\nfab_targets:\n  - jlcpcb-4layer-advanced\n')
# Daughterboards contain passive switches/LED only. All pullups, debounce and LED resistors remain on main.
for kind in ['controls','front']:
 name='alec-'+kind;d=ROOT/'boards'/name;d.mkdir(exist_ok=True);(d/'review').mkdir(exist_ok=True)
 r=node(f'(kicad_sch (version 20250114) (generator "eeschema") (uuid {uid(name)}) (paper "A4") (lib_symbols))')
 r.append(node(f'(title_block (title {q(name)}) (date "2026-09-06") (rev "v4.2 prototype"))'))
 names=BOTTOM if kind=='controls' else FRONT;n=len(names)
 add_symbol(r,symbol_def('Connector_Generic',f'Conn_01x{n:02}'),'J1',gh_mpn(n),gh(n),50,65,dict(zip(map(str,range(1,n+1)),names)),name,'https://www.jst-mfg.com/product/pdf/eng/eGH.pdf')
 if kind=='controls':
  for ref,net,y,value in [('SW1','BTN_VOL_MINUS',50,'VOL-'),('SW2','BTN_MODE',90,'MODE'),('SW3','BTN_VOL_PLUS',130,'VOL+')]:
   add_symbol(r,symbol_def('Switch','SW_Push'),ref,value,'Button_Switch_THT:SW_TH_Tactile_Omron_B3F-106x',120,y,{'1':'GND','2':net},name,'https://omronfs.omron.com/en_US/ecb/products/pdf/en-b3f.pdf','B3F-1060')
  add_symbol(r,symbol_def('Switch','SW_SPDT'),'SW4','EG1218','Alarm:EG1218',205,65,{'1':'SW_ON','2':'EN_3V3','3':'GND'},name,'https://configured-product-images.s3.amazonaws.com/2D/specs/EG1218.pdf')
 else:
  add_symbol(r,symbol_def('Switch','SW_Push'),'SW1','BATTERY','Button_Switch_SMD:SW_SPST_B3U-1000P',125,50,{'1':'GND','2':'BTN_BAT'},name,'https://omronfs.omron.com/en_US/ecb/products/pdf/en-b3u.pdf','B3U-1000P')
  add_symbol(r,defs['Review:WE_150141M173100'],'D1','150141M173100','LED_SMD:LED_RGB_Wuerth-PLCC4_3.2x2.8mm_150141M173100',125,95,{'1':'3v3','2':'LED_B_K','3':'LED_R_K','4':'LED_G_K'},name,'https://www.we-online.com/components/products/datasheet/150141M173100.pdf')
 r.append(node(f'(text {q("1:1 GH harness to main J5" if kind=="controls" else "1:1 GH harness to main J6; LED series resistors on main") } (at 40 170 0) (effects (font (size 1.5 1.5)) (justify left bottom)) (uuid {uid(name+"note")}))'))
 (d/(name+'.kicad_sch')).write_text(dump(r)+'\n')
 (d/(name+'.kicad_pro')).write_text('{}\n')
 (d/'board.yml').write_text(f'name: {name}\ndescription: Passive {kind} daughterboard for ALEC\nlayers: 2\ncopper_weight: 1oz\nthickness: 1.6mm\nfab_targets:\n  - jlcpcb-2layer-standard\n')
 (d/'checks.yml').write_text(yaml.safe_dump({'required_components':{prop(s,'Reference'):{} for s in children(r,'symbol')},'required_nets':sorted(set(names)),'bom_rules':{'require_footprint':True,'no_duplicate_refs':True}},sort_keys=False))
 (d/'fp-lib-table').write_text('(fp_lib_table (version 7) (lib (name "Alarm") (type "KiCad") (uri "${KIPRJMOD}/../../libs/footprints/Alarm.pretty") (options "") (descr "Alarm interface parts")))\n')
 print(name)
f=MAIN/'fp-lib-table';a=parse(f.read_text());a.append(node('(lib (name "Alarm") (type "KiCad") (uri "${KIPRJMOD}/../../libs/footprints/Alarm.pretty") (options "") (descr "Alarm interface parts"))'));f.write_text(dump(a)+'\n')
print('service pin order',SERVICE)
from order_parts import synchronize_board
from header_fit import apply_to_main
apply_to_main('kicad_sch')
for board in ['alec-main', 'alec-controls', 'alec-front']:
 synchronize_board(board, pcb=False)
